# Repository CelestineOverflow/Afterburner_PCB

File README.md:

# Afterburner_PCB
PCBA Files
Source Content for Afterburner controller, a temperature control and monitor board. Based of the first design made in easyeda => [afterburner easyeda project](https://oshwlab.com/celestine.s.machuca/afterburner)

# Features

- 4 pt100/1000 sensors with 2/3/4 support
- 4 independant heaters with current measuring and short circuit protection
- 1 LoadCell Amplifier 
- Power input thru USB C pd adapter up to 140w
- USB control with companion app

# Control Interface

For that please refer to [Afterburner Control Software](https://github.com/CelestineOverflow/afterburner)

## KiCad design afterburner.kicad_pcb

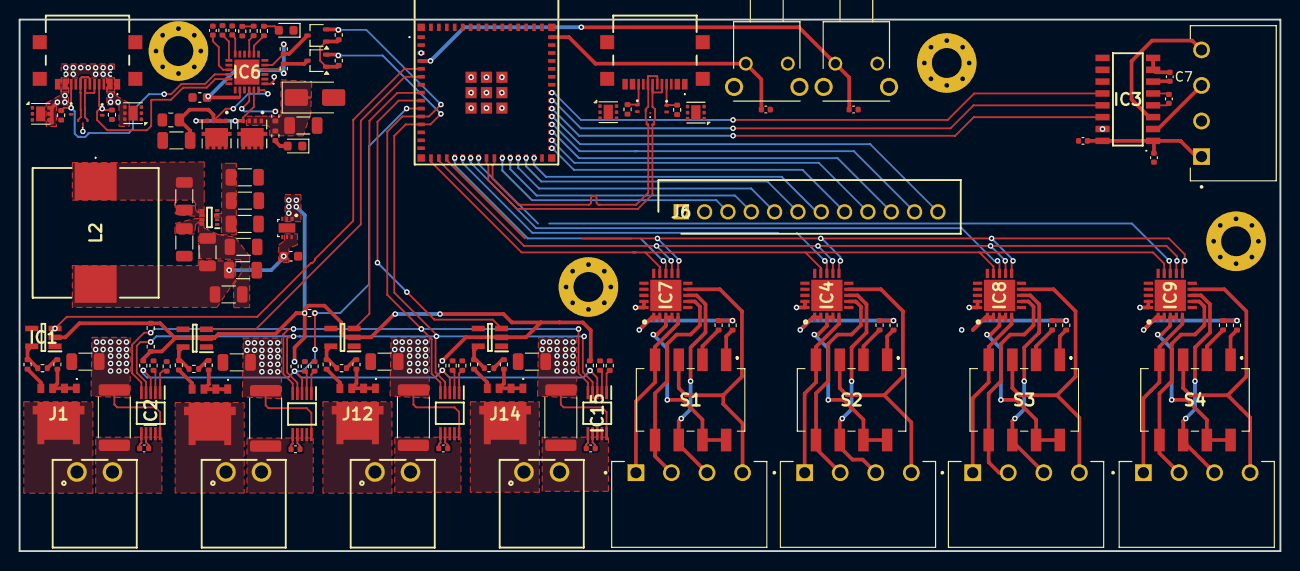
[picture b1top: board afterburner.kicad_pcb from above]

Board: 4 copper layers, 135.1 x 56.9 mm, 144 parts (0 on the bottom side), 133 nets.

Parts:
C3, C16, C18, C19, C21, C23: 100nF; C_0402_1005Metric
C4, C20, C22, C24: 4.7uF; C_1206_3216Metric
C5, C6, C7, C8: 1uF; C_0402_1005Metric
C9: 10uF; C_1206_3216Metric
C10, C11: 100nF; C_1206_3216Metric
C12, C15: 10u; C_1206_3216Metric
C13, C25: 33nF; C_1206_3216Metric
C14: 15pF; C_1206_3216Metric
C17: 1u; C_0603_1608Metric
C26: 10uF; C_0603_1608Metric
C27, C28: C; C_0402_1005Metric
Cout1: 100uF; C_1206_3216Metric
D1, D2: ESD122DMYR
D3, D5: RED; LED_0603_1608Metric
D4: D_Schottky; D_SMA
H1, H2, H4, H5: MountingHole_Pad; MountingHole_3.2mm_M3_Pad_Via
IC1, IC10, IC12, IC14: MCP1416T-E_OT; SOT95P270X145-5N
IC2, IC11, IC13, IC15: INA226AIDGSR; SOP50P490X110-10N
IC3: NAU7802SGI; SOIC127P600X175-16N
IC4, IC7, IC8, IC9: MAX31865ATP+T; QFN65P500X500X80-21N
IC5: TPS62933DRLR; SOTFL50P160X60-8N
IC6: AP33772SDKZ-13-FA01; AP33772SDKZ13FA01
IC16: ESP32-S3-MINI-1-N8; ESP32S3MINI1N8
IC17: XC6220B331ER-G; XC6220B331ERG
J1, J10, J12, J14: NTMFS5C612NLT1G
J2, J11, J13, J15: 691322310002
J3, J17, J18, J19, J20: 1803293; PHOENIX_1803293
J5, J16: UJ20-C-H-G-SMT-5-P16-TR; UJ20CHGSMT5P16TR
J6: B12B-XH-A_LF__SN_; SHDR12W64P0X250_1X12_3240X575X700P
L2: SRP1250-7R8M; SRP12507R8M
Q1, Q2: BSS138; SOT-323_SC-70
R3, R33, R40, R47: 30mΩ; R_2512_6332Metric
R4, R5, R6, R7, R8, R9, R19, R26, R34, R35, R36, R37, R38, R39, R41, R42, R43, R44, R45, R46, R48, R49, R50, R51, R52, R53, R55: 10k; R_0402_1005Metric
R10, R27, R29, R31: 430; R_0402_1005Metric
R11, R28, R30, R32: 4.3k; R_0402_1005Metric
R12, R13, R14, R16, R20, R21, R22, R23, R24, R25: 5.1k; R_0402_1005Metric
R15, R54: 4.7k; R_0402_1005Metric
R17: 5m; R_0805_2012Metric
R18: 27R; R_0402_1005Metric
Rfbb1: 10k; R_1206_3216Metric
Rfbt1: 52.3k; R_1206_3216Metric
S1, S2, S3, S4: 219-4MST; 2194MST
S5, S6: 1-1825027-1; SW_1-1825027-1
TH1: Thermistor_NTC; R_0402_1005Metric
U2, U5, U6, U9: TVS2200DRV; WSON-6-1EP_2x2mm_P0.65mm_EP1x1.6mm
U3, U4, U7, U8: TPD1E05U06DPY; Texas_DPY0002A_0.6x1mm_P0.65mm
U10, U11: AON7262E; TRANS_AONR21307

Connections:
+3.3V: Q1.1 (G), Q2.1 (G), R21.1, R22.1
+3V3: C3.1, C19.1, C21.1, C23.1, IC1.2 (VDD), IC2.6 (VS), IC3.15 (DVDD), IC4.19 (DVDD), IC4.20 (VDD), IC7.19 (DVDD), IC7.20 (VDD), IC8.19 (DVDD), IC8.20 (VDD), IC9.19 (DVDD), IC9.20 (VDD), IC10.2 (VDD), IC11.6 (VS), IC12.2 (VDD), IC13.6 (VS), IC14.2 (VDD), IC15.6 (VS), IC16.3 (3V3), IC17.1 (VOUT_1), IC17.2 (VOUT_2), J6.1, R9.2, R15.2, R39.2, R46.2, R53.2, R54.2, R55.2
+5V: C14.1, C26.2, Cout1.1, IC17.3 (CE), IC17.5 (VIN_1), IC17.6 (VIN_2), L2.2, Rfbt1.1
/ALERT_INT: IC2.3 (ALERT), IC11.3 (ALERT), IC13.3 (ALERT), IC15.3 (ALERT), IC16.10 (IO6), R9.1, R39.1, R46.1, R53.1, R55.1
/D+: D1.3 (IO2), IC16.24 (IO20), J5.A6 (DP1), J5.B6 (DP2)
/D-: D1.2 (IO1), IC16.23 (IO19), J5.A7 (DN1), J5.B7 (DN2)
/HEATER_PWM_1: IC1.3 (IN), IC16.5 (IO1)
/HEATER_PWM_2: IC10.3 (IN), IC16.6 (IO2)
/HEATER_PWM_3: IC12.3 (IN), IC16.8 (IO4)
/HEATER_PWM_4: IC14.3 (IN), IC16.9 (IO5)
/Heater_Mosfet_1/IN-: IC2.9 (IN-), J2.2, R3.1
/Heater_Mosfet_1/OUT_MOS: J1.5 (D_1), J1.6 (D_2), J1.7 (D_3), J1.8 (D_4), J1.9 (D_5), J2.1
/Heater_Mosfet_2/IN-: IC11.9 (IN-), J11.2, R33.1
/Heater_Mosfet_2/OUT_MOS: J10.5 (D_1), J10.6 (D_2), J10.7 (D_3), J10.8 (D_4), J10.9 (D_5), J11.1
/Heater_Mosfet_3/IN-: IC13.9 (IN-), J13.2, R40.1
/Heater_Mosfet_3/OUT_MOS: J12.5 (D_1), J12.6 (D_2), J12.7 (D_3), J12.8 (D_4), J12.9 (D_5), J13.1
/Heater_Mosfet_4/IN-: IC15.9 (IN-), J15.2, R47.1
/Heater_Mosfet_4/OUT_MOS: J14.5 (D_1), J14.6 (D_2), J14.7 (D_3), J14.8 (D_4), J14.9 (D_5), J15.1
/LCD_BL: IC16.31 (IO35), J6.8
/LCD_CS: IC16.27 (IO47), J6.5
/LCD_DC: IC16.28 (IO33), J6.6
/LCD_RST: IC16.29 (IO34), J6.7
/LCD_SCL: IC16.26 (IO26), J6.4
/LCD_SDA: IC16.25 (IO21), J6.3
/LDCL_DRDY: IC3.12 (DRDY), IC16.38 (IO42)
/LDCL_SCLK: IC3.13 (SCLK), IC16.37 (IO41)
/LDCL_SDIO: IC3.14 (SDIO), IC16.36 (IO40)
/MCU/BOOT: C27.2, IC16.4 (IO0), S5.2
/MCU/ENABLE: C28.2, IC16.45 (EN), S6.2
/MISO: IC4.14 (SDO), IC7.14 (SDO), IC8.14 (SDO), IC9.14 (SDO), IC16.16 (IO12)
/MOSI: IC4.11 (SDI), IC7.11 (SDI), IC8.11 (SDI), IC9.11 (SDI), IC16.18 (IO14)
/PD/CC1: IC6.17 (CC1), J16.A5 (CC1), R14.1, U7.1 (I/O)
/PD/CC2: IC6.16 (CC2), J16.B5 (CC2), R16.1, U8.1 (I/O)
/PD/IFB: C16.1, IC6.15 (IFB)
/PD/NTC: IC6.13 (OTP), TH1.1
/PD/PD_INT: R25.2, R26.1
/PD/PD_INT_5V: IC6.9 (INT), R25.1
/PD/PD_LED: IC6.8 (LED), R20.1
/PD/PWR_EN: IC6.23 (PWR_EN), U10.4, U11.4
/PD/SCL_5V: IC6.5 (SCL), Q1.3 (D), R23.2
/PD/SDA_5V: IC6.4 (SDA), Q2.3 (D), R24.2
/PD/USB_N: D2.2 (IO1), J16.A7 (DN1), J16.B7 (DN2)
/PD/USB_P: D2.3 (IO2), J16.A6 (DP1), J16.B6 (DP2)
/PD/V5V: C17.1, IC6.20 (V5V), R23.1, R24.1
/PD/V18: C18.1, IC6.12 (V18)
/PD/VBUS: IC6.1 (ISENP), J16.A4 (VBUS_1), J16.B4 (VBUS_2), R17.1, U6.4 (IN), U6.5 (IN), U6.6 (IN), U9.4 (IN), U9.5 (IN), U9.6 (IN)
/PD/VBUS_SENSED: C12.1, IC6.24 (VCC), R17.2, U10.1, U10.2, U10.3
/PD/VCC: C9.2, C10.1, C15.1, C25.1, D4.1 (K), IC5.3 (VIN), R18.2, R19.1, U11.1, U11.2, U11.3
/PD/VOUT: IC6.22 (VOUT), R18.1
/SCK: IC4.12 (SCLK), IC7.12 (SCLK), IC8.12 (SCLK), IC9.12 (SCLK), IC16.17 (IO13)
/SCL: IC2.5 (SCL), IC11.5 (SCL), IC13.5 (SCL), IC15.5 (SCL), IC16.11 (IO7), Q1.2 (S), R15.1, R21.2
/SDA: IC2.4 (SDA), IC11.4 (SDA), IC13.4 (SDA), IC15.4 (SDA), IC16.12 (IO8), Q2.2 (S), R22.2, R54.1
/SS1: IC7.13 (~CS), IC16.19 (IO15)
/SS2: IC4.13 (~CS), IC16.20 (IO16)
/SS3: IC8.13 (~CS), IC16.21 (IO17)
/SS4: IC9.13 (~CS), IC16.22 (IO18)
/TP_IRQ: IC16.35 (IO39), J6.12
/TP_RST: IC16.34 (IO38), J6.11
/TP_SCL: IC16.33 (IO37), J6.10
/TP_SDA: IC16.32 (IO36), J6.9
/Temp Sensor 1/430R: R10.1, S1.2
/Temp Sensor 1/4300R: R11.1, S1.1
/Temp Sensor 1/FORCE_N: IC7.9 (FORCE-), J18.04, S1.3
/Temp Sensor 1/FORCE_P: IC7.5 (FORCE+), J18.01, S1.4
/Temp Sensor 1/ISENSOR: IC7.3 (REFIN-), IC7.4 (ISENSOR), S1.7, S1.8
/Temp Sensor 1/RTDIN_N: IC7.8 (RTDIN-), J18.03, S1.6
/Temp Sensor 1/RTDIN_P: IC7.7 (RTDIN+), J18.02, S1.5
/Temp Sensor 2/430R: R27.1, S2.2
/Temp Sensor 2/4300R: R28.1, S2.1
/Temp Sensor 2/FORCE_N: IC4.9 (FORCE-), J17.04, S2.3
/Temp Sensor 2/FORCE_P: IC4.5 (FORCE+), J17.01, S2.4
/Temp Sensor 2/ISENSOR: IC4.3 (REFIN-), IC4.4 (ISENSOR), S2.7, S2.8
/Temp Sensor 2/RTDIN_N: IC4.8 (RTDIN-), J17.03, S2.6
/Temp Sensor 2/RTDIN_P: IC4.7 (RTDIN+), J17.02, S2.5
/Temp Sensor 3/430R: R29.1, S3.2
/Temp Sensor 3/4300R: R30.1, S3.1
/Temp Sensor 3/FORCE_N: IC8.9 (FORCE-), J19.04, S3.3
/Temp Sensor 3/FORCE_P: IC8.5 (FORCE+), J19.01, S3.4
/Temp Sensor 3/ISENSOR: IC8.3 (REFIN-), IC8.4 (ISENSOR), S3.7, S3.8
/Temp Sensor 3/RTDIN_N: IC8.8 (RTDIN-), J19.03, S3.6
/Temp Sensor 3/RTDIN_P: IC8.7 (RTDIN+), J19.02, S3.5
/Temp Sensor 4/430R: R31.1, S4.2
/Temp Sensor 4/4300R: R32.1, S4.1
/Temp Sensor 4/FORCE_N: IC9.9 (FORCE-), J20.04, S4.3
/Temp Sensor 4/FORCE_P: IC9.5 (FORCE+), J20.01, S4.4
/Temp Sensor 4/ISENSOR: IC9.3 (REFIN-), IC9.4 (ISENSOR), S4.7, S4.8
/Temp Sensor 4/RTDIN_N: IC9.8 (RTDIN-), J20.03, S4.6
/Temp Sensor 4/RTDIN_P: IC9.7 (RTDIN+), J20.02, S4.5
/USB _CONTROL/CC1: J5.A5 (CC1), R12.1, U3.1 (I/O)
/USB _CONTROL/CC2: J5.B5 (CC2), R13.1, U4.1 (I/O)
/USB _CONTROL/VBUS: J5.A4 (VBUS_1), J5.B4 (VBUS_2), U2.4 (IN), U2.5 (IN), U2.6 (IN), U5.4 (IN), U5.5 (IN), U5.6 (IN)
GND: C3.2, C4.2, C5.2, C7.2, C8.2, C9.1, C10.2, C12.2, C13.1, C15.2, C16.2, C17.2, C18.2, C19.2, C20.2, C21.2, C22.2, C23.2, C24.2, C25.2, C26.1, C27.1, C28.1, Cout1.2, D1.1 (GROUND), D2.1 (GROUND), D3.1 (K), D4.2 (A), D5.1 (K), H1.1, H2.1, H4.1, H5.1, IC1.4 (GND), IC2.7 (GND), IC3.7 (REFN), IC3.8 (AVSS), IC3.9 (DVSS), IC4.6 (FORCE2), IC4.10 (GND2), IC4.15 (DGND), IC4.16 (GND1), IC4.21 (EP), IC5.4 (GND), IC6.3 (GND_1), IC6.25 (GND_2), IC7.6 (FORCE2), IC7.10 (GND2), IC7.15 (DGND), IC7.16 (GND1), IC7.21 (EP), IC8.6 (FORCE2), IC8.10 (GND2), IC8.15 (DGND), IC8.16 (GND1), IC8.21 (EP), IC9.6 (FORCE2), IC9.10 (GND2), IC9.15 (DGND), IC9.16 (GND1), IC9.21 (EP), IC10.4 (GND), IC11.7 (GND), IC12.4 (GND), IC13.7 (GND), IC14.4 (GND), IC15.7 (GND), IC16.1 (GND_1), IC16.2 (GND_2), IC16.42 (GND_3), IC16.43 (GND_4), IC16.46 (GND_5), IC16.47 (GND_6), IC16.48 (GND_7), IC16.49 (GND_8), IC16.50 (GND_9), IC16.51 (GND_10), IC16.52 (GND_11), IC16.53 (GND_12), IC16.54 (GND_13), IC16.55 (GND_14), IC16.56 (GND_15), IC16.57 (GND_16), IC16.58 (GND_17), IC16.59 (GND_18), IC16.60 (GND_19), IC16.61 (GND_20), IC16.62 (GND_21), IC16.63 (GND_22), IC16.64 (GND_23), IC16.65 (GND_24), IC16.66 (GND_25), IC16.67 (GND_26), IC16.68 (GND_27), IC16.69 (GND_28), IC16.70 (GND_29), IC16.71 (GND_30), IC16.72 (GND_31), IC16.73 (GND_32), IC17.4 (VSS), IC17.7 (EP), J3.02, J5.A1 (GND_1), J5.B1 (GND_2), J5.MP1, J5.MP2, J5.MP3, J5.MP4, J6.2, J16.A1 (GND_1), J16.B1 (GND_2), J16.MP1, J16.MP2, J16.MP3, J16.MP4, R7.2, R8.2, R12.2, R13.2, R14.2, R16.2, R26.2, R37.2, R38.2, R44.2, R45.2, R51.2, R52.2, Rfbb1.2, S5.1, S6.1, TH1.2, U2.1 (GND), U2.2 (GND), U2.3 (GND), U2.7 (GND), U3.2 (GND), U4.2 (GND), U5.1 (GND), U5.2 (GND), U5.3 (GND), U5.7 (GND), U6.1 (GND), U6.2 (GND), U6.3 (GND), U6.7 (GND), U7.2 (GND), U8.2 (GND), U9.1 (GND), U9.2 (GND), U9.3 (GND), U9.7 (GND)
unnamed: D3.2 (A), R19.2
unnamed: D5.2 (A), R20.2
unnamed: IC1.5 (OUT), R4.1, R5.1
unnamed: IC2.2 (A0), R8.1
unnamed: IC2.1 (A1), R7.1
unnamed: C5.1, C8.1, IC3.1 (REFP), IC3.16 (AVDD/LDO), J3.01
unnamed: C7.1, IC3.6 (VBG)
unnamed: IC3.2 (VIN1N), J3.03
unnamed: IC3.3 (VIN1P), J3.04
unnamed: C6.1, IC3.4 (VIN2N)
unnamed: C6.2, IC3.5 (VIN2P)
unnamed: IC4.1 (BIAS), IC4.2 (REFIN+), R27.2, R28.2
unnamed: C11.1, IC5.6 (BST)
unnamed: C14.2, IC5.8 (FB), Rfbb1.1, Rfbt1.2
unnamed: C13.2, IC5.7 (SS)
unnamed: C11.2, IC5.5 (SW), L2.1
unnamed: IC7.1 (BIAS), IC7.2 (REFIN+), R10.2, R11.2
unnamed: IC8.1 (BIAS), IC8.2 (REFIN+), R29.2, R30.2
unnamed: IC9.1 (BIAS), IC9.2 (REFIN+), R31.2, R32.2
unnamed: IC10.5 (OUT), R34.1, R35.1
unnamed: IC11.2 (A0), R38.1
unnamed: IC11.1 (A1), R37.1
unnamed: IC12.5 (OUT), R41.1, R42.1
unnamed: IC13.2 (A0), R45.1
unnamed: IC13.1 (A1), R44.1
unnamed: IC14.5 (OUT), R48.1, R49.1
unnamed: IC15.2 (A0), R52.1
unnamed: IC15.1 (A1), R51.1
unnamed: J1.4 (G), R5.2
unnamed: J1.1 (S_1), J1.2 (S_2), J1.3 (S_3), R6.2
unnamed: J10.4 (G), R35.2
unnamed: J10.1 (S_1), J10.2 (S_2), J10.3 (S_3), R36.2
unnamed: J12.4 (G), R42.2
unnamed: J12.1 (S_1), J12.2 (S_2), J12.3 (S_3), R43.2
unnamed: J14.4 (G), R49.2
unnamed: J14.1 (S_1), J14.2 (S_2), J14.3 (S_3), R50.2
unnamed: R4.2, R6.1
unnamed: R34.2, R36.1
unnamed: R41.2, R43.1
unnamed: R48.2, R50.1
VCC: C4.1, C20.1, C22.1, C24.1, IC2.8 (VBUS), IC2.10 (IN+), IC11.8 (VBUS), IC11.10 (IN+), IC13.8 (VBUS), IC13.10 (IN+), IC15.8 (VBUS), IC15.10 (IN+), R3.2, R33.2, R40.2, R47.2

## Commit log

2025-08-05 Added stuff
2025-08-11 small changes
2025-08-14 added readme
2025-08-22 lots of change
